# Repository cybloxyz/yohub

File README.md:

# YOHUB v0.1.0
meet YOHUBv0.1.0! a compact size dual function of hardware! aesthetic and usable as an USB HUB!
this USB hub was deisgned with kicad

## why?
i made this immediately after my laptop's touchpad broken, i realize that i only have one USB port and it is already taken for my mouse, i confuse how do i attach the flashdrive or anything else.

## what is this?
keychain that you could use as an usual USB Hub, powered by SL2.1A! really compact and suitable for any bag ofc :3 oh and it also has transparent case! a YoCase

and here is the YoCase version

here are some features of YOHUB v0.1.0

> 3x USB-A

> 1x USB-C

> 1x USB-c as upstream port

> keychain hole

> compact size! 6.8x3.8 (in cm)

## schema and pcb
here is the screenshot of schema and pcb editor
here is the wiring diagram of Yohub, followed guide but i made the USB_A more than the USB_C since my laptop is lack of USB_A but have 3 port of USB_C.

## components
| Id | Designator | Footprint | Qty | Description | Supplier | Part Number | Price/Unit (IDR) | Total (IDR) | Link |
|:--:|:---|:---|:--:|:---|:---|:---|:---:|:---:|:---|
| 1 | C1, C2, C3, C4, C5, C7, C8, C11 | 0603 | 8 | 1uF Capacitor | LCSC | C15849 | 150 | 1.200 | [🔗 Link](https://www.lcsc.com/product-detail/C15849.html) |
| 2 | U1 | SO16 | 1 | SL2.1A (USB Hub IC) | LCSC | C92463 | 4.500 | 4.500 | [🔗 Link](https://www.lcsc.com/product-detail/C92463.html) |
| 3 | C6, C9, C10 | 0603 | 3 | 100nF Capacitor | LCSC | C14663 | 100 | 300 | [🔗 Link](https://www.lcsc.com/product-detail/C14663.html) |
| 4 | J1, J4 | USB-C 16P | 2 | USB-C Female GCT | LCSC | C719112 | 3.500 | 7.000 | [🔗 Link](https://www.lcsc.com/product-detail/C719112.html) |
| 5 | R1, R2 | 0603 | 2 | 10k Resistor | LCSC | C25804 | 50 | 100 | [🔗 Link](https://www.lcsc.com/product-detail/C25804.html) |
| 6 | R5, R6 | 0603 | 2 | 5.1k Resistor | LCSC | C25905 | 50 | 100 | [🔗 Link](https://www.lcsc.com/product-detail/C25905.html) |
| 7 | J2, J3, J5 | USB_A_Rec | 3 | USB 2.0 Type A | LCSC | C51922 | 2.500 | 7.500 | [🔗 Link](https://www.lcsc.com/product-detail/C51922.html) |
| | | | | **ESTIMASI TOTAL** | | | | **Rp20.700** | |

note: this is only the component not the pcb, we recommend to use JLCPCB

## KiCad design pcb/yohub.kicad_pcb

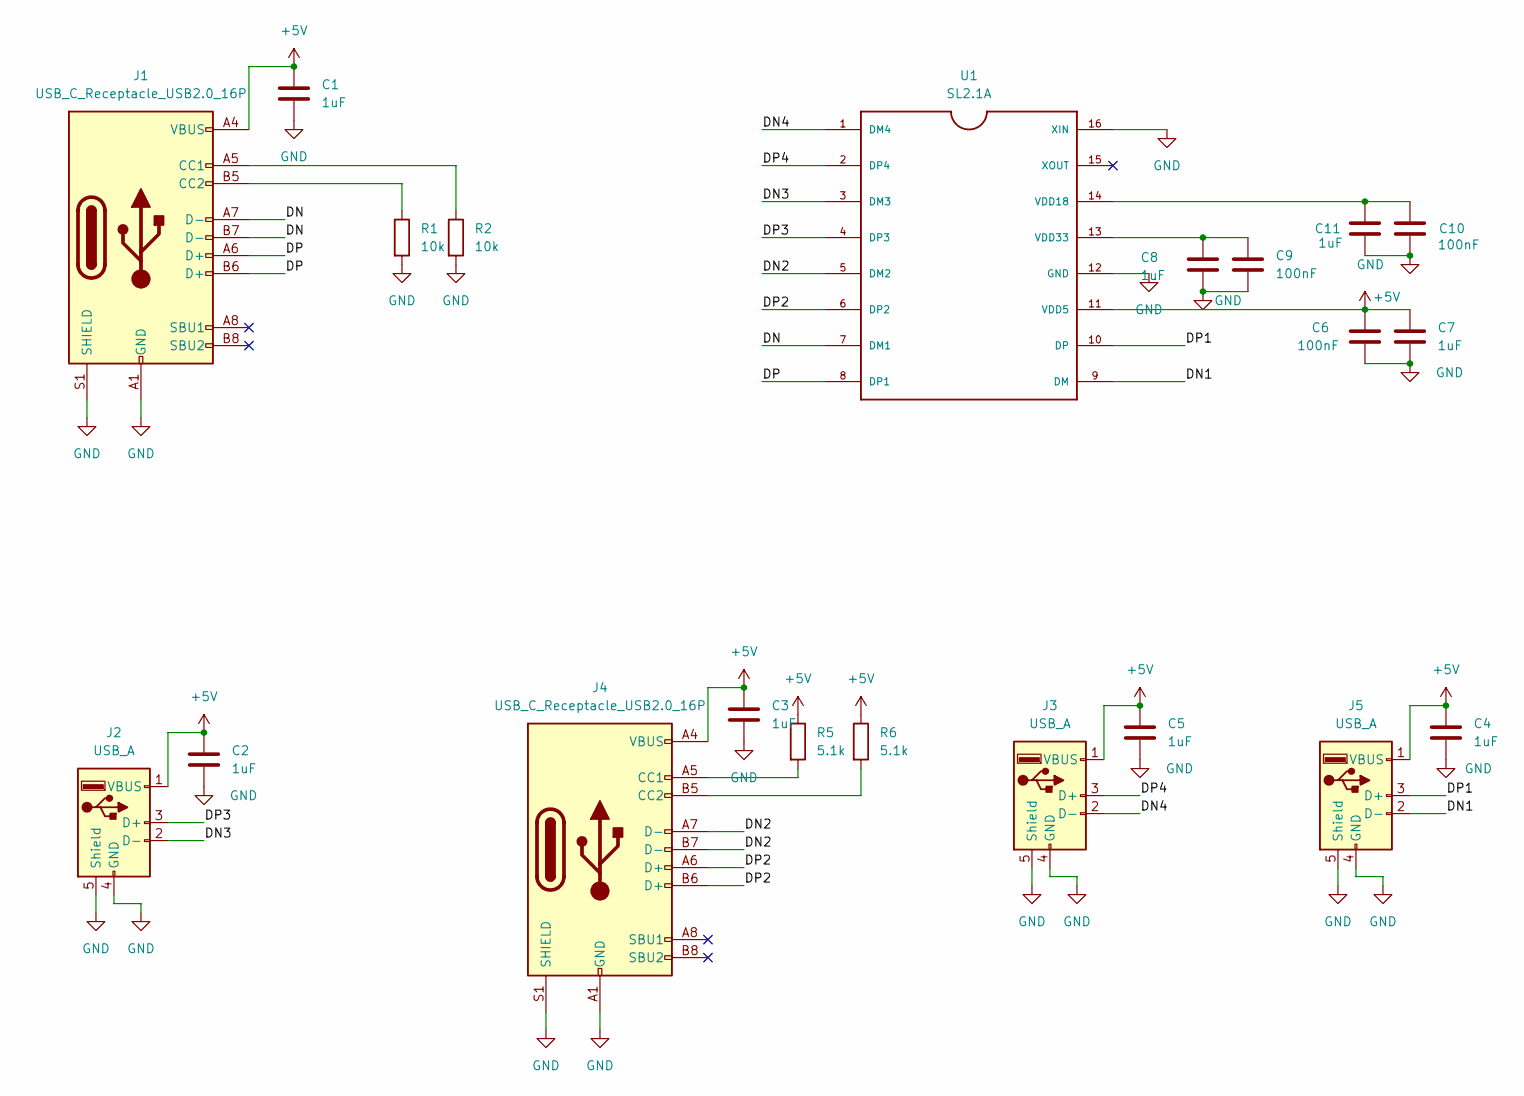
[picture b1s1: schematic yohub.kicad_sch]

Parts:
C1, C2, C3, C4, C5, C7, C8, C11: 1uF; C_0603_1608Metric_Pad1.08x0.95mm_HandSolder
C6, C9, C10: 100nF; C_0603_1608Metric_Pad1.08x0.95mm_HandSolder
J1, J4: USB_C_Receptacle_USB2.0_16P; USB_C_Receptacle_GCT_USB4105-xx-A_16P_TopMnt_Horizontal
J2, J3, J5: USB_A; USB_A_Receptacle_GCT_USB1046
R1, R2: 10k; R_0603_1608Metric_Pad0.98x0.95mm_HandSolder
R5, R6: 5.1k; R_0603_1608Metric_Pad0.98x0.95mm_HandSolder
U1: SL2.1A; SO16

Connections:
+5V: C1.1, C2.1, C3.1, C4.1, C5.1, C6.1, C7.1, J1.A4 (VBUS), J1.A9 (VBUS), J1.B4 (VBUS), J1.B9 (VBUS), J2.1 (VBUS), J3.1 (VBUS), J4.A4 (VBUS), J4.A9 (VBUS), J4.B4 (VBUS), J4.B9 (VBUS), J5.1 (VBUS), R5.1, R6.1, U1.11 (VDD5)
/DN: J1.A7 (D-), J1.B7 (D-), U1.7 (DM1)
/DN1: J5.2 (D-), U1.9 (DM)
/DN2: J4.A7 (D-), J4.B7 (D-), U1.5 (DM2)
/DN3: J2.2 (D-), U1.3 (DM3)
/DN4: J3.2 (D-), U1.1 (DM4)
/DP: J1.A6 (D+), J1.B6 (D+), U1.8 (DP1)
/DP1: J5.3 (D+), U1.10 (DP)
/DP2: J4.A6 (D+), J4.B6 (D+), U1.6 (DP2)
/DP3: J2.3 (D+), U1.4 (DP3)
/DP4: J3.3 (D+), U1.2 (DP4)
GND: C1.2, C2.2, C3.2, C4.2, C5.2, C6.2, C7.2, C8.2, C9.2, C10.2, C11.2, J1.A1 (GND), J1.A12 (GND), J1.B1 (GND), J1.B12 (GND), J1.S1 (SHIELD), J2.4 (GND), J2.5 (Shield), J3.4 (GND), J3.5 (Shield), J4.A1 (GND), J4.A12 (GND), J4.B1 (GND), J4.B12 (GND), J4.S1 (SHIELD), J5.4 (GND), J5.5 (Shield), R1.2, R2.2, U1.12 (GND), U1.16 (XIN)
unnamed: J1.A5 (CC1), R2.1
unnamed: J1.B5 (CC2), R1.1
unnamed: J4.A5 (CC1), R5.2
unnamed: J4.B5 (CC2), R6.2
unnamed: C10.1, C11.1, U1.14 (VDD18)
unnamed: C8.1, C9.1, U1.13 (VDD33)

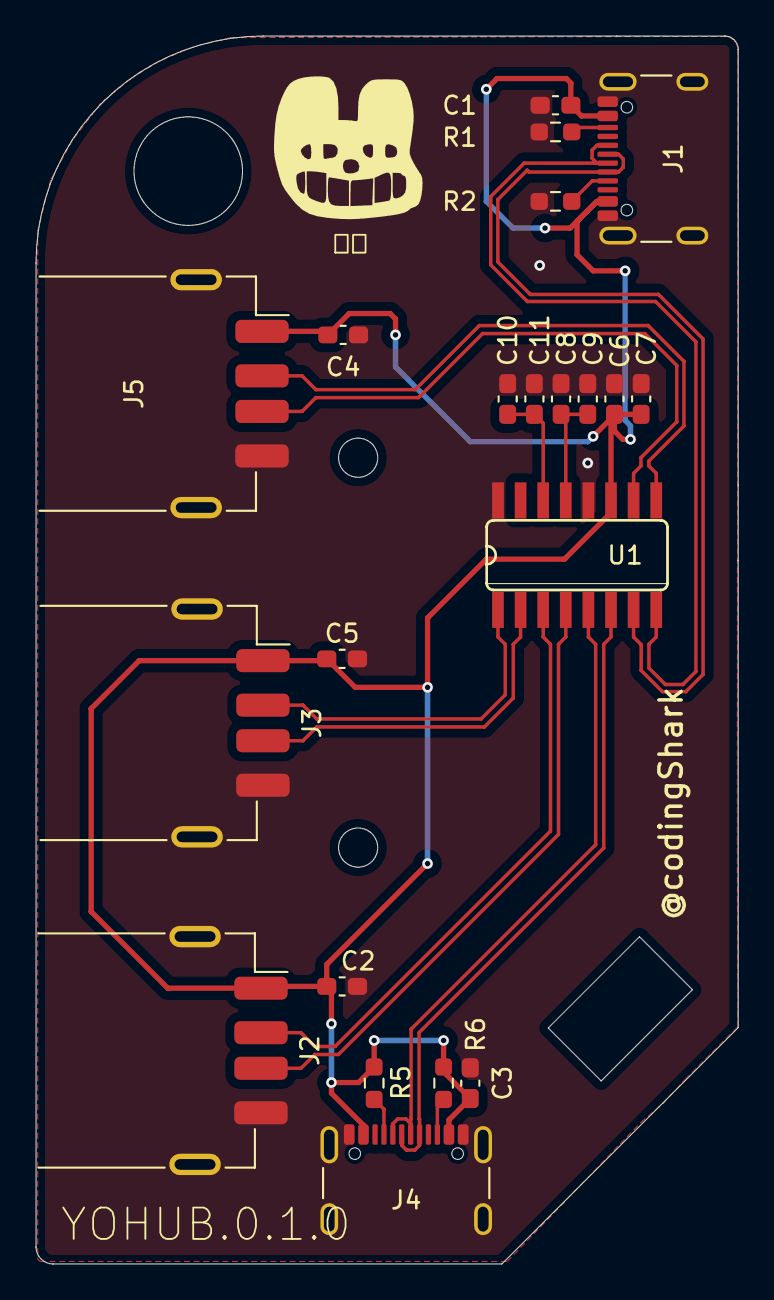
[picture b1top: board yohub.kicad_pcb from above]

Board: 2 copper layers, 39.4 x 69.0 mm, 22 parts (0 on the bottom side), 18 nets.

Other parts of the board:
head: mao; head

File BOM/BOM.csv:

Id;Designator;Footprint;Qty;Description;Supplier;Ref/Part Number;Price_Unit_IDR;Total_Price_IDR
1;C2,C7,C5,C3,C4,C1,C11,C8;C_0603_1608Metric;8;1uF Capacitor;LCSC;C15849;150;1200
2;U1;SO16;1;SL2.1A (USB Hub IC);LCSC;C92463;4500;4500
3;C10,C6,C9;C_0603_1608Metric;3;100nF Capacitor;LCSC;C14663;100;300
4;J1,J4;USB_C_Receptacle (16P);2;USB-C Female GCT;LCSC;C719112;3500;7000
5;R2,R1;R_0603_1608Metric;2;10k Resistor;LCSC;C25804;50;100
6;R5,R6;R_0603_1608Metric;2;5.1k Resistor;LCSC;C25905;50;100
7;J3,J5,J2;USB_A_Receptacle;3;USB 2.0 Type A;LCSC;C51922;2500;7500

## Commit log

2026-04-16 first initialize
2026-04-17 almost done!
2026-04-17 readme readme readme
2026-04-17 add links!
2026-04-29 add case and it called YoCase
